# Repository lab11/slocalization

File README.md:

# slocalization
High-Fidelity Localization of Slow Energy-Harvesting Tags

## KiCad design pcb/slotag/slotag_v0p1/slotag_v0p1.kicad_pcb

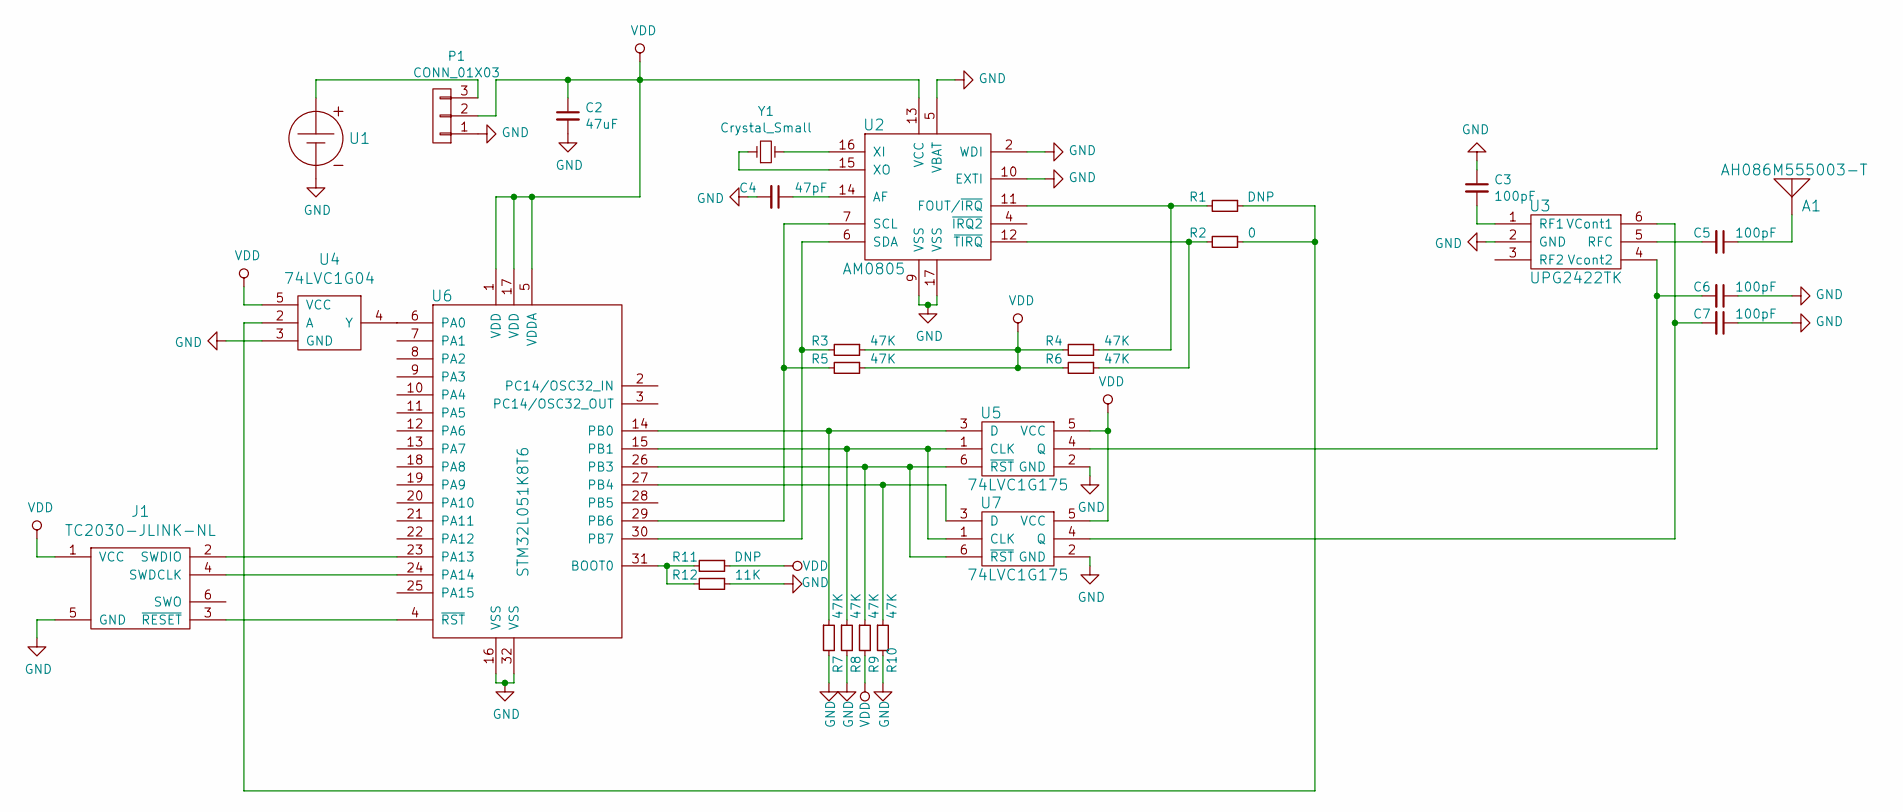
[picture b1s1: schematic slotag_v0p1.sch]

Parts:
A1: ANT; AH086M; ManPartNo AH086M555003-T
C2: 47uF; C_0805; ManPartNo TLNN476M010R6000
C3, C5, C6, C7: 100pF; C_0402; ManPartNo GRM1555C1H101JA01J
C4: 47pF; C_0402; ManPartNo GRM1555C1H470JA01D
J1: TC2030-JLINK-NL; TC2030
P1: CONN_01X03; Pin_Header_Straight_1x03
R1, R11: DNP; R_0402
R2: 0; R_0402; ManPartNo ERJ-2GE0R00X
R3, R4, R5, R6, R7, R8, R9, R10: 47K; R_0402; ManPartNo ERJ-2RKF4702X
R12: 11K; R_0402; ManPartNo ERJ-2RKF1102X
U1: SOLAR_CELL; AM-1417; ManPartNo AM-1417CA
U2: AM0805; QFN-16-1EP_3x3mm_Pitch0.5mm
U3: UPG2422TK; MINIMOLD-6; ManPartNo UPG2422TK-A
U4: 74LVC1G04; SOT-353; ManPartNo 74LVC1G04GW,125
U5, U7: 74LVC1G175; SOT-363; ManPartNo 74LVC1G175GW,125
U6: STM32L051K8T6; LQFP-32_7x7mm_Pitch0.8mm; ManPartNo STM32L051K8T6
Y1: Crystal_Small; XTAL-3.2mm-1.5mm; ManPartNo ABS07-32.768KHZ-7-T

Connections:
GND: C2.2, C3.1, C4.2, C6.1, C7.1, J1.5 (GND), P1.1, R7.2, R8.2, R10.2, R12.1, U1.2, U2.2 (WDI), U2.5 (VBAT), U2.9 (VSS), U2.10 (EXTI), U2.17 (VSS), U3.2 (GND), U4.3 (GND), U5.2 (GND), U6.16 (VSS), U6.32 (VSS), U7.2 (GND)
unnamed: A1.1, C5.1, C5.2, U3.5 (RFC)
unnamed: C3.2, U3.1 (RF1)
unnamed: C4.1, U2.14 (AF)
unnamed: C6.2, U3.4 (Vcont2), U5.4 (Q)
unnamed: C7.2, U3.6 (VCont1), U7.4 (Q)
unnamed: J1.2 (SWDIO), U6.23 (PA13)
unnamed: J1.3 (~RESET), U6.4 (~RST)
unnamed: J1.4 (SWDCLK), U6.24 (PA14)
unnamed: P1.3, U1.1
unnamed: R1.1, R2.1, U4.2 (A)
unnamed: R1.2, R4.1, U2.11 (FOUT/~IRQ)
unnamed: R2.2, R6.1, U2.12 (~TIRQ)
unnamed: R3.2, U2.6 (SDA), U6.30 (PB7)
unnamed: R5.2, U2.7 (SCL), U6.29 (PB6)
unnamed: R7.1, U5.3 (D), U6.14 (PB0)
unnamed: R8.1, U5.1 (CLK), U6.15 (PB1), U7.1 (CLK)
unnamed: R9.1, U5.6 (~RST), U6.26 (PB3), U7.6 (~RST)
unnamed: R10.1, U6.27 (PB4), U7.3 (D)
unnamed: R11.2, R12.2, U6.31 (BOOT0)
unnamed: U2.15 (XO), Y1.1
unnamed: U2.16 (XI), Y1.2
unnamed: U4.4 (Y), U6.6 (PA0)
VDD: C2.1, J1.1 (VCC), P1.2, R3.1, R4.2, R5.1, R6.2, R9.2, R11.1, U2.13 (VCC), U4.5 (VCC), U5.5 (VCC), U6.1 (VDD), U6.5 (VDDA), U6.17 (VDD), U7.5 (VCC)

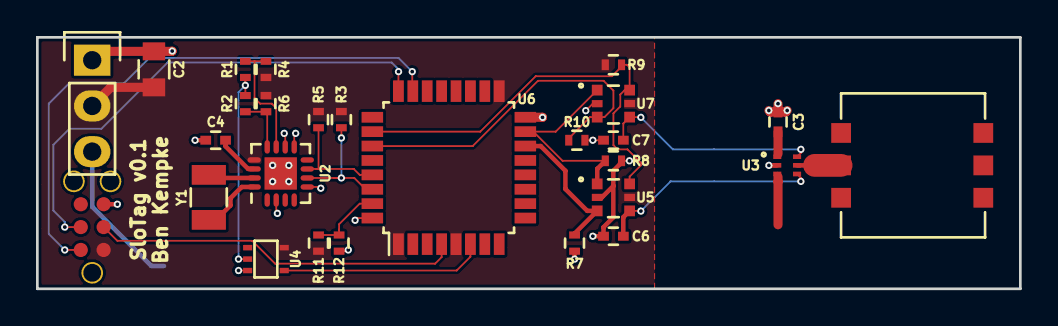
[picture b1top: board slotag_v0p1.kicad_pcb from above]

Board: 2 copper layers, 54.6 x 14.0 mm, 28 parts (1 on the bottom side), 24 nets.

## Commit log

2016-02-20 adding first pass at 2-layer slocalization tag
2016-02-21 adding component part numbers
2016-02-21 minor cosmetic fixes
2016-02-21 adding gerbers for slotag
2016-02-22 adding slotag BOM
2016-02-29 adding candidate standby test code
2016-02-29 example sleep code compiles
2016-02-29 major progress: able to configure Ambiq RTC over I2C to produce square wave on FOUT pin
2016-03-01 Ambiq RTC now triggers periodic (1 Hz) wakeup events. Need to work on reducing average power consumption
2016-03-01 1 Hz PN code sequencing now works
2016-03-02 Turn on link-time-optimization
    This lets gcc treat all of the objects as one giant program and do
    optimization over the whole thing. Gets big wins for stuff like
    register writes because inlining can occur much more aggressively.
    Halves the code size of the current project and shaves ~350 us off
    the startup time.
2016-03-02 Pull more efficient startup assembly from submodule
2016-03-02 Kill of `HAL_Init`, doesn't seem to matter
2016-03-02 Move I2CxHandle out of global memory
    This is a bit a trick, since it needs to be global but is only used
    in the cold boot case. What we do then is make a global pointer to
    the structure and then zero-init and fill a copy only on the cold
    boot path where it's used.
    This trade-off makes the 1-time true cold boot a little bit slower
    but the long-running warm-boot faster [also trades off a little
2016-03-02 Remove GPIO struct from globals
    Same theory as previous commit. Ultimately this is pushing towards
    being able to eliminate the bss altogether
2016-03-02 Move clock config to only cold boot path
2016-03-02 Skip tradtional reset handler
2016-03-04 adding true gold sequences to tag code along with the code to generate them
2016-03-06 backscatter confirmed
2016-03-07 Update slotag_v0p1.csv
    Fix commas so that github doesn't yell about invalid csv
2016-03-09 out_tag_3ft.bin starting to come out of the noise
2016-03-10 adding manchester encoding to tag data stream
2016-03-10 positive results with out_manchester_works.bin
2016-03-12 now modified to work at faster update rate (out_manchester_fast_works.bin)
2016-03-15 best AGC avoidance yet
2016-03-22 modifications to support antenna diversity
2016-03-22 adding support for octave
2017-01-04 adding barebones uwb_bandstitching code
2017-01-04 barebones code will continuously send and receive at START_FREQ
2017-01-04 final candidate code for bandstitching
2017-01-15 working code
2017-01-17 adding external reference selectors
2017-01-17 adding all newly created oot files
2017-01-17 adding block to do windowed accumulations
2017-01-18 getting close
2017-01-19 adding USRP parser
2017-01-19 finally extracting good-quality CIRs from data
2017-01-19 better bounds
2017-01-20 improvements to bandstitching code
2017-02-05 getting close to properly locating identifying tag CIR
2017-02-09 new tag code, etc
2017-02-11 adding code to generate sequences which have less overall dynamic range
2017-02-11 candidate code to increase frequency content
2017-02-11 spectrally flat transmit
2017-02-13 actually generating intelligible tag CIRs
2017-02-13 better measurement timing estimates
2017-02-13 best to just do tag frequency analysis offline for now
2017-02-16 adding support for multiple USRP receivers
2017-03-07 adding candidate code to perform extremely wideband bandstitching
2017-03-13 actual working ellipse-based localization
2017-03-15 rearranged to do one sweep per call to uwb_bandstitching.py
2017-03-15 candidate code for simultaneous TXRX on all USRPs
2017-03-17 aliasing issues
2017-03-18 working on bandstitching and tag CIR extraction
2017-03-18 adding script to process all paths in localization setup
2017-03-22 finding a consistent way of determining phase offset between USRPs
2017-03-22 adding in determination of phase offset into overair_data bias
2017-03-22 adding in direct CIR to recorded observations
2017-03-22 adding script to compute real location
2017-03-22 script to automate back-and-forth data collection
2017-03-22 fixing bugs from last commit
2017-03-23 better performance with bigger spacing
2017-03-23 need to chop some off at the end of each recording as well during multi-usrp recordings
2017-03-23 need to trim cal data as well
2017-03-29 adding modifications to SBX driver
2017-03-29 better to just do one transmitter at a time
2017-03-29 working backscatter localization
2017-03-30 results processing
2017-04-03 adding cir vs integration time analysis
2017-04-05 adding analysis for CIR variance
2017-04-09 pn code
2017-04-09 forgot to commit this file
2017-04-09 adding pn code identification
2017-04-10 adding more analyses
2018-01-25 checkpoint on unchecked-in code
2018-01-26 adding long range code
2018-01-27 better USRP packet reception performance
2018-01-27 send_buff_size increased getting rid of underflows
2018-02-06 no PN
2018-02-09 add onezero code
2018-02-09 easier interface
2018-02-13 work in progress towards needed time
2018-02-13 frequency drift
2018-02-13 flexible samples
2018-02-13 fix mixing signal to use all bands
2018-02-14 plot all time
2018-02-14 adapt for missing bands
2018-02-14 wrapper to run repeated
2018-02-14 add data analysis
2018-02-14 scale graph automatically
2018-02-14 nlos
2018-02-16 changes that were sitting
